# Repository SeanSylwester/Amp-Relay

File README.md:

# Amp-Relay
Audio controlled relay to switch on an audio amplifier when connecting to a Bluetooth receiver

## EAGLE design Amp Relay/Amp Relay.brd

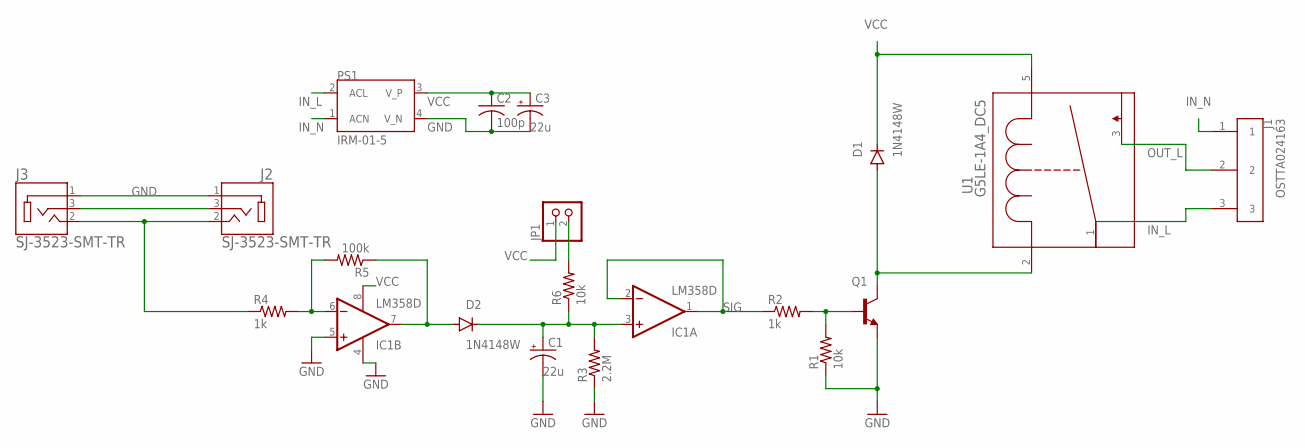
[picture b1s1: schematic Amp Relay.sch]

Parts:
C1, C3: WE-CAP
C2: 100p; C0805
D1, D2: 1N4148W; SOD123
IC1: LM358D; SO08
J1: OSTTA024163
J2, J3: SJ-3523-SMT-TR; CUI_SJ-3523-SMT-TR
JP1: PINHD-1X2; 1X02
PS1: IRM-01-5; CONV_IRM-01-5
Q1: BC849SMD; SOT23-BEC
R1, R6: 10k; R1206
R2, R4: 1k; R0805
R3: 2.2M; R1206
R5: 100k; R1206
U1: G5LE-1A4_DC5; RELAY_G5LE-1A

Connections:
B: Q1.B, R1.2, R2.2
C: D1.A, Q1.C, U1.2 (1)
GND: C1.-, C2.2, C3.-, IC1.4 (V-), IC1.5 (+IN), J2.1, J3.1, PS1.4 (V_N), Q1.E, R1.1, R3.1
IN_L: J1.3, PS1.2 (ACL), U1.1 (2)
IN_N: J1.1, PS1.1 (ACN)
unnamed: JP1.2, R6.2
unnamed: J2.2, J3.2, R4.1
unnamed: IC1.6 (-IN), R4.2, R5.2
unnamed: D2.A, IC1.7 (OUT), R5.1
unnamed: C1.+, D2.C, IC1.3 (+IN), R3.2, R6.1
unnamed: J2.3, J3.3
OUT_L: J1.2, U1.3
SIG: IC1.1 (OUT), IC1.2 (-IN), R2.1
VCC: C2.1, C3.+, D1.C, IC1.8 (V+), JP1.1, PS1.3 (V_P), U1.5 (4)

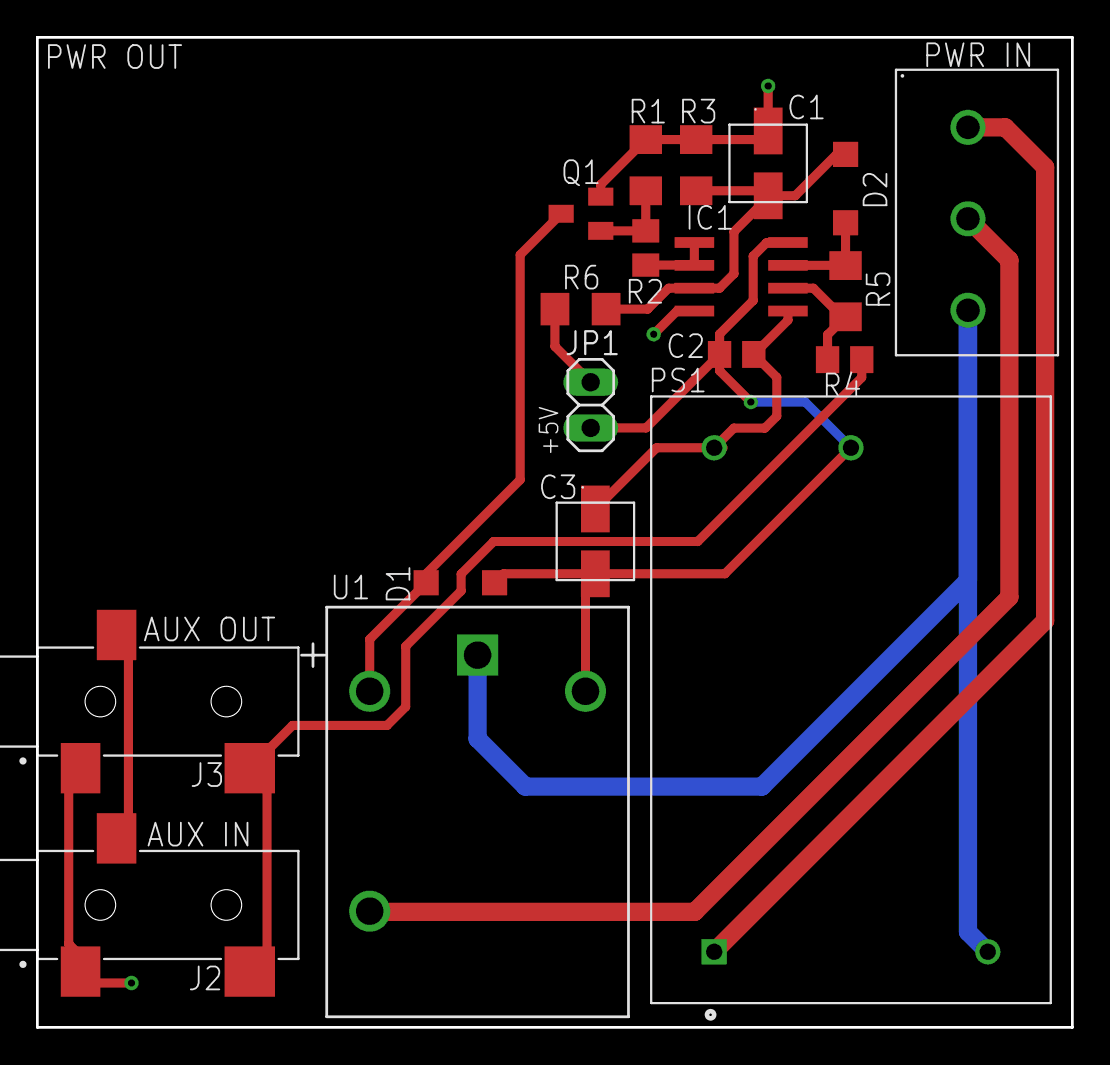
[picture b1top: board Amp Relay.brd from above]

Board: 2 copper layers, 57.5 x 55.0 mm, 19 parts (0 on the bottom side), 14 nets.

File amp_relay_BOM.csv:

Quantity,Part Number,Manufacturer Part Number
1,Z3116-ND,G5LE-1A4 DC5
1,MMBT2222A-FDICT-ND,MMBT2222A-7-F
2,RMCF1206JT10K0CT-ND,RMCF1206JT10K0
2,RNCP0805FTD1K00CT-ND,RNCP0805FTD1K00
2,1N4148W-FDICT-ND,1N4148W-7-F
1,RMCF1206JT100KCT-ND,RMCF1206JT100K
1,497-1591-1-ND,LM358DT
1,RMCF1206JT2M20CT-ND,RMCF1206JT2M20
2,732-8413-1-ND,8.65E+11
2,CP-3523SJCT-ND,SJ-3523-SMT-TR
1,Q227-ND,738W-X2/03
1,1866-2998-ND,IRM-01-5
1,311-1111-1-ND,CC0805JRNPO9BN101
1,ED2581-ND,OSTTA034163
1,EG5617-ND,RA11131121

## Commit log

2019-06-08 aux ground and terminal block soldermask fix
2019-06-08 added BOM
2019-06-12 added toggle switch, and cutouts for the aux ports
